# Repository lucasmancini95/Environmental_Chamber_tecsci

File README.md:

# Environmental_Chamber_tecsci
Environmental Chamber Firmware for the ESP32.

Hardware:
ESP32
BME280 - humidity, temperature and pressure sensor - bosh
Humidifier - 2.4Mhz
Air Pump
Relay x2

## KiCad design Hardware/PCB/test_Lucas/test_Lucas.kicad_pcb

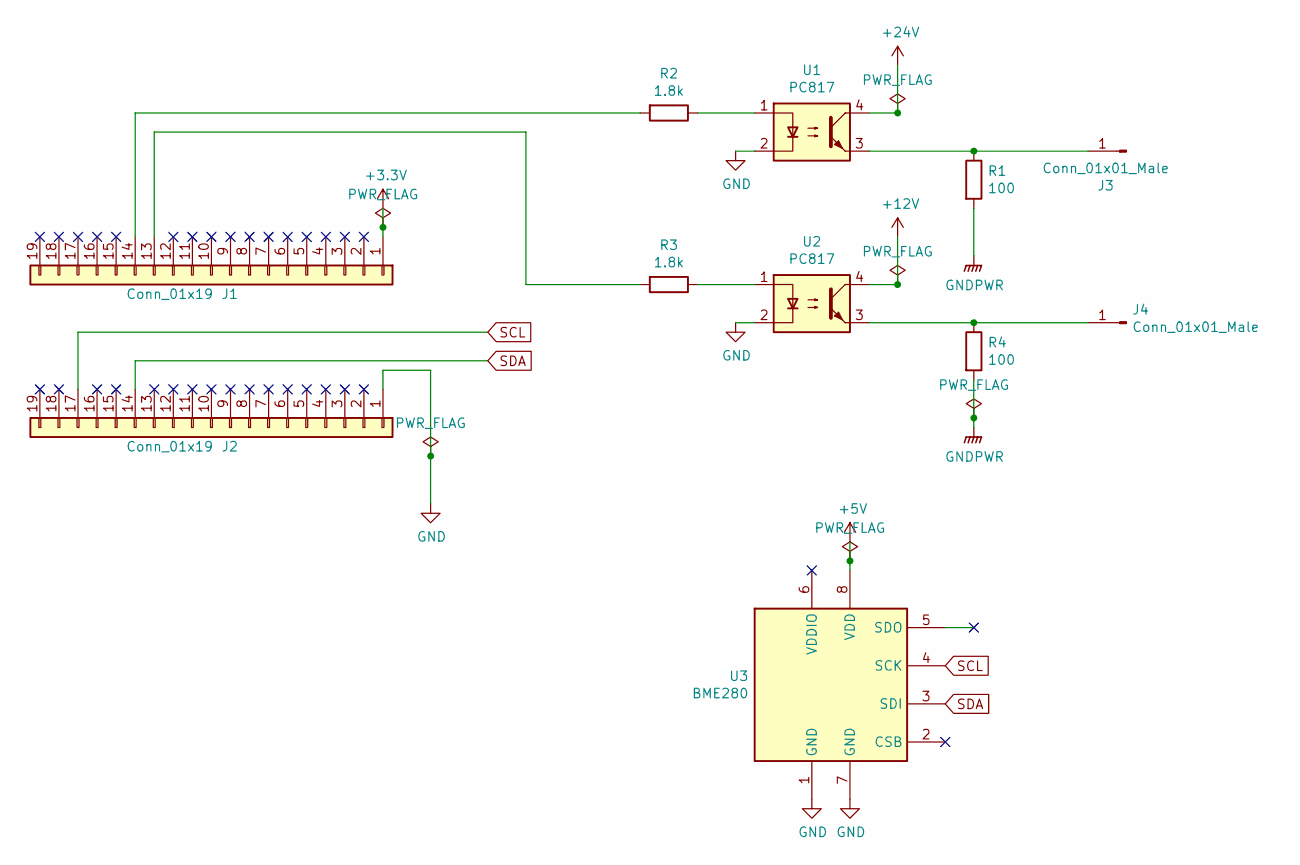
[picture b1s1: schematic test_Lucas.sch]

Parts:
J1, J2: Conn_01x19; PinSocket_1x19_P2.54mm_Vertical
J3, J4: Conn_01x01_Male; PinHeader_1x01_P2.54mm_Vertical
R1, R4: 100; R_1206_3216Metric_Pad1.42x1.75mm_HandSolder
R2, R3: 1.8k; R_1206_3216Metric_Pad1.42x1.75mm_HandSolder
U1, U2: PC817; DIP-4_W7.62mm
U3: BME280; Bosch_LGA-8_2.5x2.5mm_P0.65mm_ClockwisePinNumbering

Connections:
+3V3: J1.1
+5V: U3.8 (VDD)
+12V: U2.4
+24V: U1.4
GND: J2.1, U1.2, U2.2, U3.1 (GND), U3.7 (GND)
GNDPWR: R1.2, R4.2
unnamed: J1.13, R3.2
unnamed: J1.14, R2.2
unnamed: J3.1, R1.1, U1.3
unnamed: J4.1, R4.1, U2.3
unnamed: R2.1, U1.1
unnamed: R3.1, U2.1
SCL: J2.17, U3.4 (SCK)
SDA: J2.14, U3.3 (SDI)

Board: 2 copper layers, 11 parts (0 on the bottom side), 10 nets, no tracks yet.

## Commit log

2019-11-03 commit test
2019-11-03 Upload of the testing code - this version doesn t use the console
2019-11-03 This is a simple code for arduino to first make a proof concept of the environmental chamber control
2019-11-04 Update of 4 11 19 - adding the addapted PID module
2019-11-13 Uploading ENvironmental_chamber_V1 WITH console and TCP connection
2019-11-14 Add files via upload
    First PCB Upload - V0 test
